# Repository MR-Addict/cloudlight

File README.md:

# Cloudlight

这是一个模拟云彩闪烁物联网项目，使用了定制的 ESP32 开发板和 3D 打印的外壳。

**项目功能**

- [x] 可动态修改 WiFi 的 SSID 和密码
- [x] 有 OTA 功能，可以通过 HTTP 请求更新固件
- [x] 有方便管理的 Web 界面，可以查看设备信息和控制设备
- [x] 有完善的 RESTful API 接口，可以通过 HTTP 请求控制数目和亮度

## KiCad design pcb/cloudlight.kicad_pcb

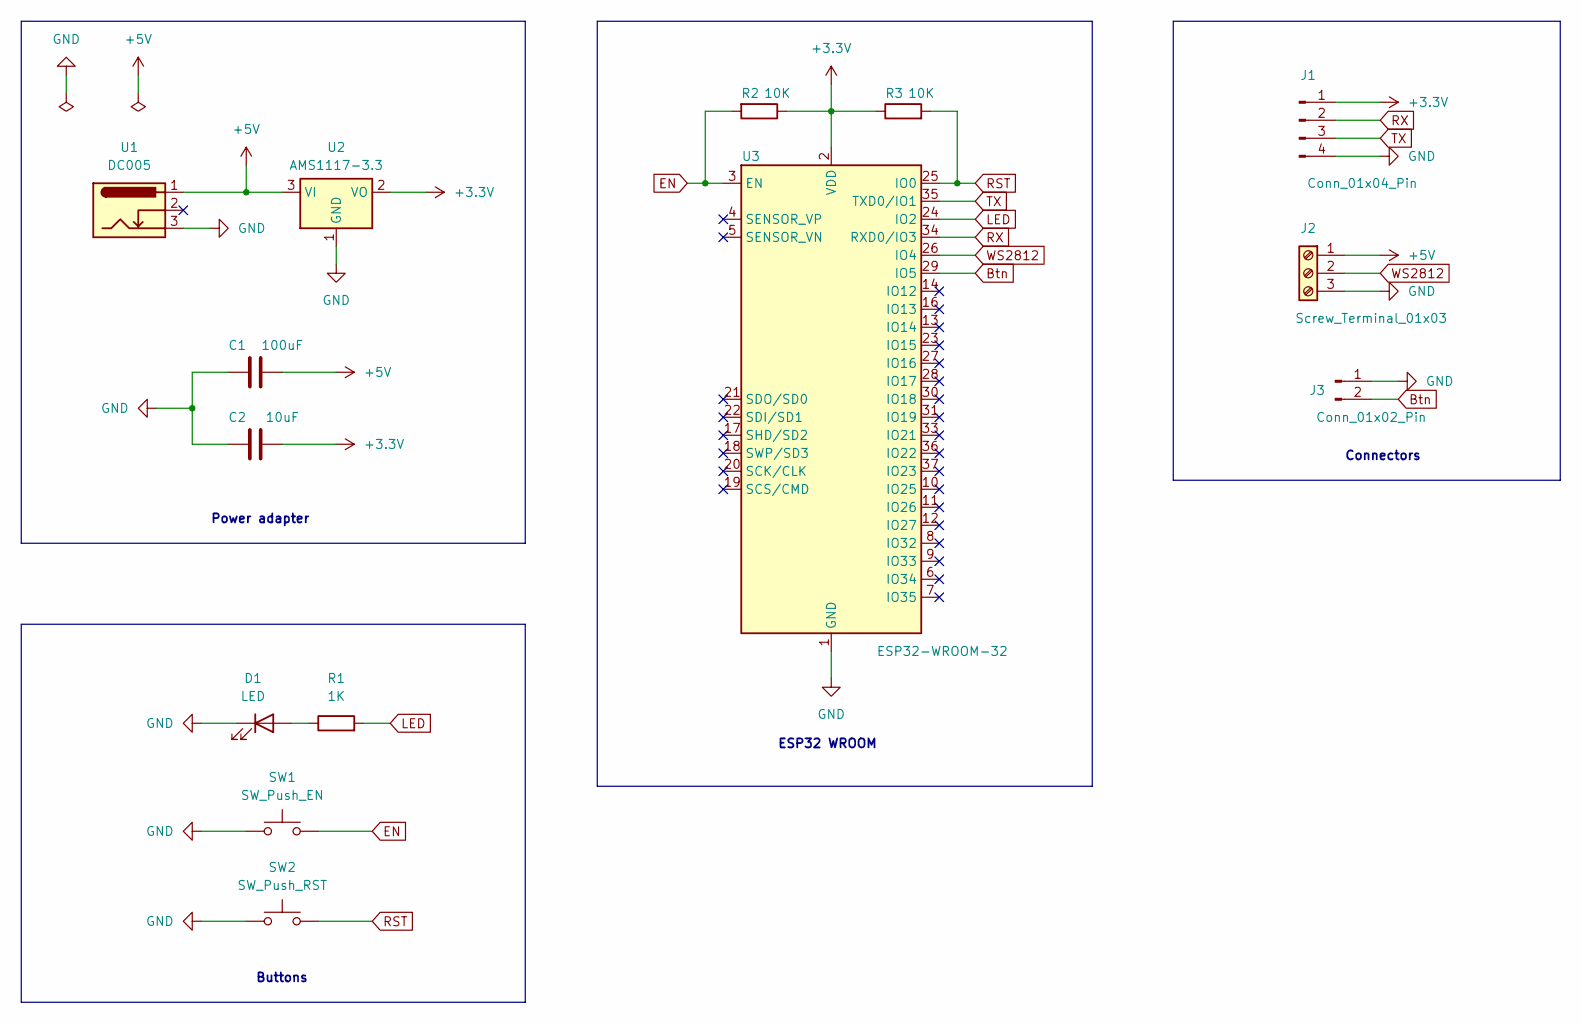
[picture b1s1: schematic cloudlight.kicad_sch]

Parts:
C1: 100uF; C_0805_2012Metric
C2: 10uF; C_0805_2012Metric
D1: LED; LED_0805_2012Metric
J1: Conn_01x04_Pin; PinHeader_1x04_P2.54mm_Vertical
J2: Screw_Terminal_01x03; TerminalBlock_bornier-3_P5.08mm
J3: Conn_01x02_Pin; PinHeader_1x02_P2.54mm_Vertical
R1: 1K; R_0805_2012Metric
R2, R3: 10K; R_0805_2012Metric
SW1: SW_Push_EN; SW_SPST_FSMSM
SW2: SW_Push_RST; SW_SPST_FSMSM
U1: DC005
U2: AMS1117-3.3; SOT-223-3_TabPin2
U3: ESP32-WROOM-32

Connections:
+3.3V: C2.2, J1.1, R2.1, R3.1, U2.2 (VO), U3.2 (VDD)
+5V: C1.2, J2.1, U1.1, U2.3 (VI)
Btn: J3.2, U3.29 (IO5)
EN: R2.2, SW1.2, U3.3 (EN)
GND: C1.1, C2.1, D1.1 (K), J1.4, J2.3, J3.1, SW1.1, SW2.1, U1.3, U2.1 (GND), U3.1 (GND), U3.15 (GND), U3.38 (GND), U3.39 (GND)
LED: R1.2, U3.24 (IO2)
unnamed: D1.2 (A), R1.1
RST: R3.2, SW2.2, U3.25 (IO0)
RX: J1.2, U3.34 (RXD0/IO3)
TX: J1.3, U3.35 (TXD0/IO1)
WS2812: J2.2, U3.26 (IO4)

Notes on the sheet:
Power adapter
Connectors
Buttons
ESP32 WROOM

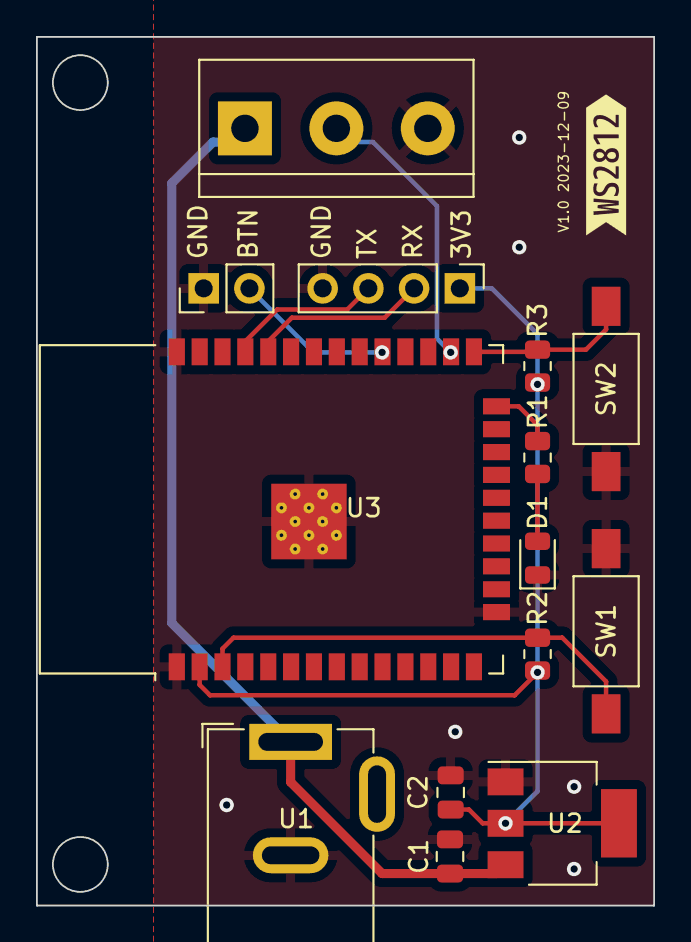
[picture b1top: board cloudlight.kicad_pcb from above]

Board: 2 copper layers, 34.3 x 48.3 mm, 15 parts (0 on the bottom side), 11 nets.

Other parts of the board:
kibuzzard-65742BE8: G***; kibuzzard-65742BE8

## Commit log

2023-12-12 feat: add setup page for editing credentials
2023-12-12 feat: finish home page
2023-12-13 feat: add LED controller
2024-03-21 feat: automatically remember last light state and brightness
2024-03-25 feat: support dynamic wifi and led configuration
